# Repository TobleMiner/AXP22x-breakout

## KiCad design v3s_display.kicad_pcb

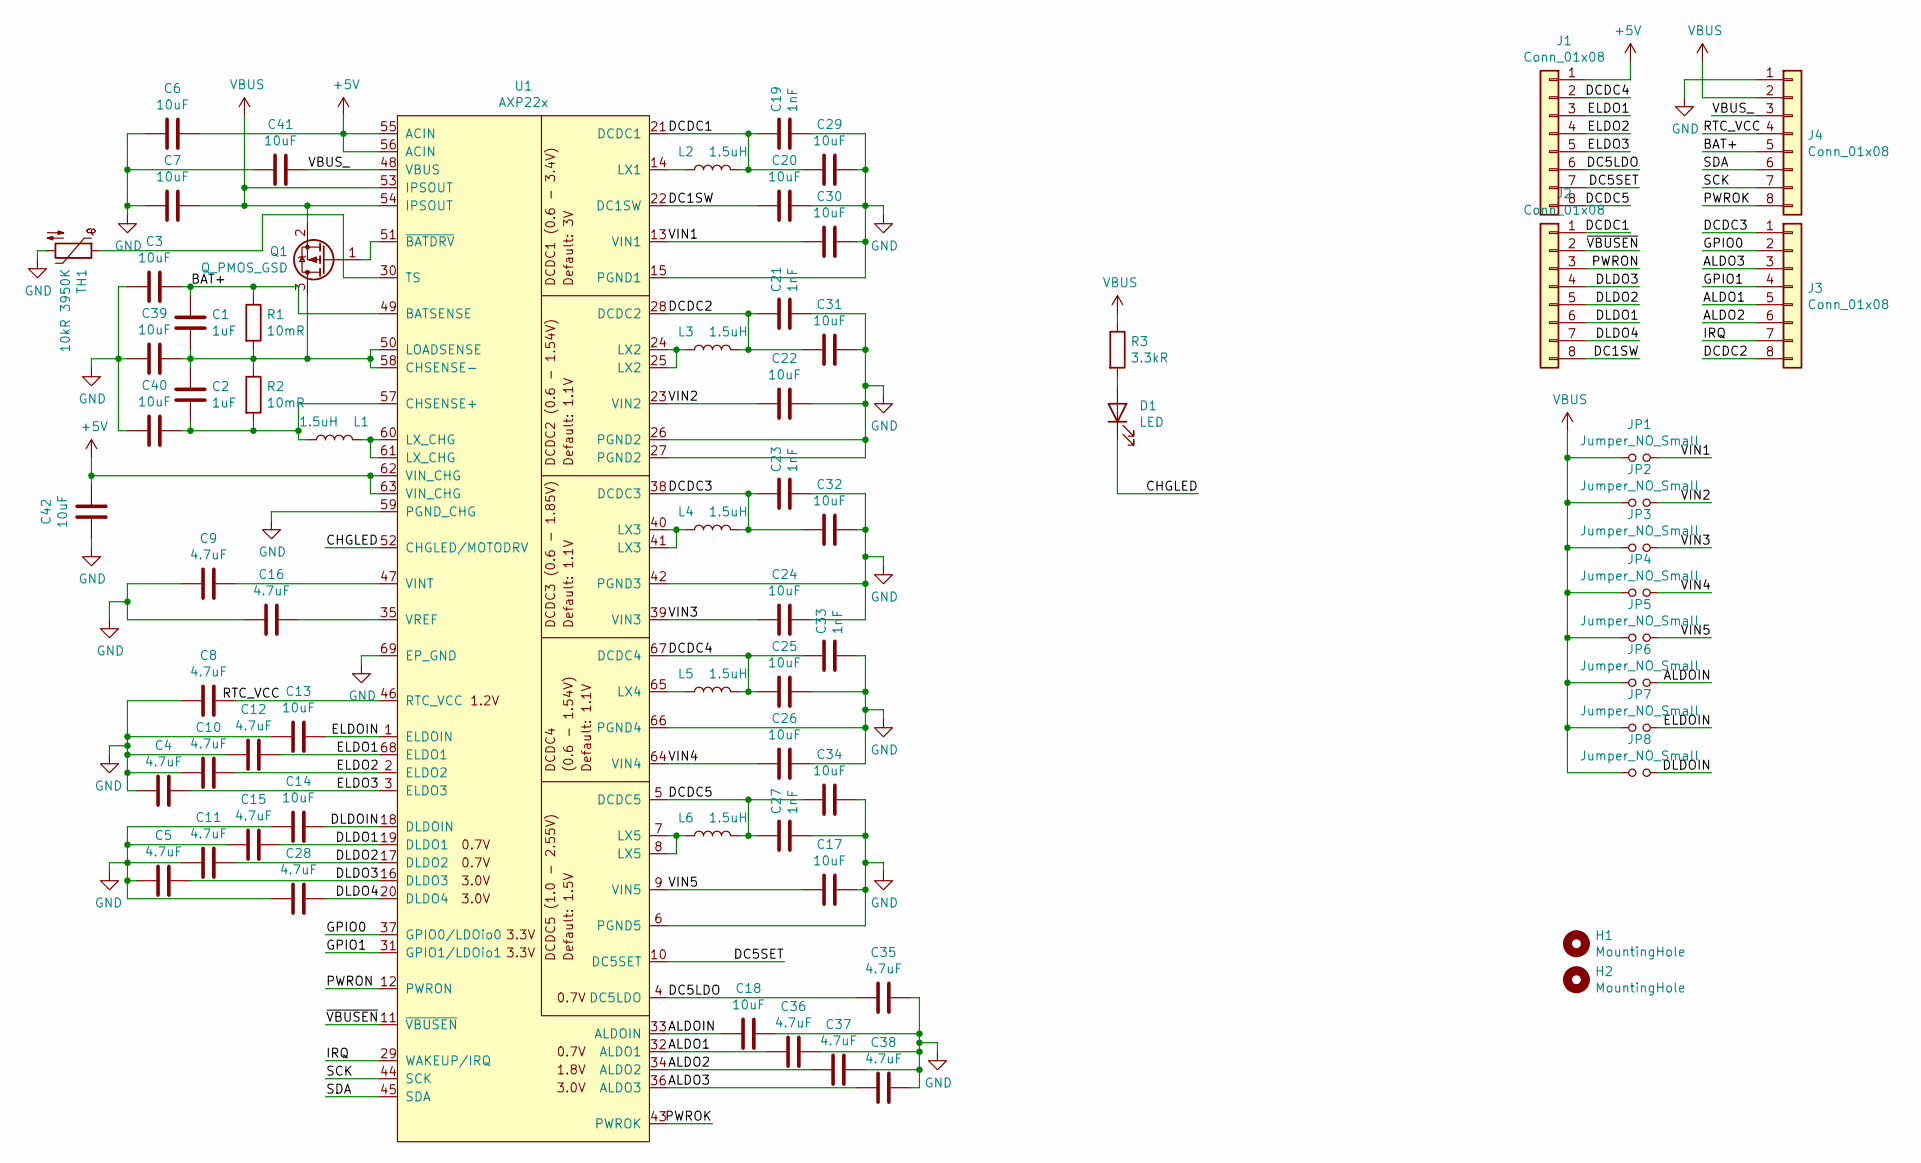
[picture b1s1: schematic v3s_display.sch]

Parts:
C1, C2: 1uF; C_0402_1005Metric; LCSC C52923
C3, C6, C7, C13, C14, C17, C18, C20, C22, C24, C25, C26, C29, C30, C31, C32, C34, C39, C40, C41, C42: 10uF; C_0603_1608Metric; LCSC C19702
C4, C5, C8, C9, C10, C11, C12, C15, C16, C28, C35, C36, C37, C38: 4.7uF; C_0402_1005Metric; LCSC C23733
C19, C21, C23, C27, C33: 1nF; C_0402_1005Metric; LCSC C1523
D1: LED; LED_0603_1608Metric; LCSC C2286
H1, H2: MountingHole; ToolingHole_JLCSMT
J1, J2, J3, J4: Conn_01x08; PinHeader_1x08_P2.54mm_Vertical
JP1, JP2, JP3, JP4, JP5, JP6, JP7, JP8: Jumper_NO_Small; PinHeader_1x02_P2.54mm_Vertical
L1, L2, L3, L4, L5, L6: 1.5uH; L_Taiyo-Yuden_MD-3030; LCSC C56594
Q1: Q_PMOS_GSD; SOT-23; LCSC C15127
R1, R2: 10mR; R_0805_2012Metric; LCSC C270927
R3: 3.3kR; R_0402_1005Metric; LCSC C25890
TH1: 10kR 3950K; R_0805_2012Metric; LCSC C51597
U1: AXP22x; QFN-68-1EP_8x8mm_P0.4mm_EP5.2x5.2mm_ThermalVias; LCSC C81850

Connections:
+5V: C6.1, C42.1, J1.1, U1.55 (ACIN), U1.56 (ACIN), U1.62 (VIN_CHG), U1.63 (VIN_CHG)
/ALDO1: C36.1, J3.5, U1.32 (ALDO1)
/ALDO2: C37.1, J3.6, U1.34 (ALDO2)
/ALDO3: C38.1, J3.3, U1.36 (ALDO3)
/ALDOIN: C18.2, JP6.2, U1.33 (ALDOIN)
/BAT+: C1.1, C3.1, J4.5, R1.1, U1.49 (BATSENSE)
/CHGLED: D1.1 (K), U1.52 (CHGLED/MOTODRV)
/DC1SW: C20.2, J2.8, U1.22 (DC1SW)
/DC5LDO: C35.1, J1.6, U1.4 (DC5LDO)
/DC5SET: J1.7, U1.10 (DC5SET)
/DCDC1: C19.1, C29.2, J2.1, L2.2, U1.21 (DCDC1)
/DCDC2: C21.1, C31.2, J3.8, L3.2, U1.28 (DCDC2)
/DCDC3: C23.1, C32.2, J3.1, L4.2, U1.38 (DCDC3)
/DCDC4: C25.2, C33.1, J1.2, L5.2, U1.67 (DCDC4)
/DCDC5: C27.1, C34.2, J1.8, L6.2, U1.5 (DCDC5)
/DLDO1: C15.2, J2.6, U1.19 (DLDO1)
/DLDO2: C11.2, J2.5, U1.17 (DLDO2)
/DLDO3: C5.2, J2.4, U1.16 (DLDO3)
/DLDO4: C28.2, J2.7, U1.20 (DLDO4)
/DLDOIN: C14.2, JP8.2, U1.18 (DLDOIN)
/ELDO1: C12.2, J1.3, U1.68 (ELDO1)
/ELDO2: C10.2, J1.4, U1.2 (ELDO2)
/ELDO3: C4.2, J1.5, U1.3 (ELDO3)
/ELDOIN: C13.2, JP7.2, U1.1 (ELDOIN)
/GPIO0: J3.2, U1.37 (GPIO0/LDOio0)
/GPIO1: J3.4, U1.31 (GPIO1/LDOio1)
/IRQ: J3.7, U1.29 (WAKEUP/IRQ)
/PWROK: J4.8, U1.43 (PWROK)
/PWRON: J2.3, U1.12 (PWRON)
/RTC_VCC: C8.2, J4.4, U1.46 (RTC_VCC)
/SCK: J4.7, U1.44 (SCK)
/SDA: J4.6, U1.45 (SDA)
/VBUS_: C41.1, J4.3, U1.48 (VBUS)
/VIN1: C30.2, JP1.2, U1.13 (VIN1)
/VIN2: C22.2, JP2.2, U1.23 (VIN2)
/VIN3: C24.2, JP3.2, U1.39 (VIN3)
/VIN4: C26.2, JP4.2, U1.64 (VIN4)
/VIN5: C17.2, JP5.2, U1.9 (VIN5)
/~VBUSEN: J2.2, U1.11 (~VBUSEN)
GND: C3.2, C4.1, C5.1, C6.2, C7.2, C8.1, C9.1, C10.1, C11.1, C12.1, C13.1, C14.1, C15.1, C16.1, C17.1, C18.1, C19.2, C20.1, C21.2, C22.1, C23.2, C24.1, C25.1, C26.1, C27.2, C28.1, C29.1, C30.1, C31.1, C32.1, C33.2, C34.1, C35.2, C36.2, C37.2, C38.2, C39.2, C40.2, C41.2, C42.2, J4.1, TH1.2, U1.6 (PGND5), U1.15 (PGND1), U1.26 (PGND2), U1.27 (PGND2), U1.42 (PGND3), U1.59 (PGND_CHG), U1.66 (PGND4), U1.69 (EP_GND)
unnamed: C1.2, C2.1, C39.1, Q1.3 (D), R1.2, R2.1, U1.50 (LOADSENSE), U1.58 (CHSENSE-)
unnamed: C2.2, C40.1, L1.2, R2.2, U1.57 (CHSENSE+)
unnamed: C9.2, U1.47 (VINT)
unnamed: C16.2, U1.35 (VREF)
unnamed: D1.2 (A), R3.2
unnamed: L1.1, U1.60 (LX_CHG), U1.61 (LX_CHG)
unnamed: L2.1, U1.14 (LX1)
unnamed: L3.1, U1.24 (LX2), U1.25 (LX2)
unnamed: L4.1, U1.40 (LX3), U1.41 (LX3)
unnamed: L5.1, U1.65 (LX4)
unnamed: L6.1, U1.7 (LX5), U1.8 (LX5)
unnamed: Q1.1 (G), U1.51 (~BATDRV)
unnamed: TH1.1, U1.30 (TS)
VBUS: C7.1, J4.2, JP1.1, JP2.1, JP3.1, JP4.1, JP5.1, JP6.1, JP7.1, JP8.1, Q1.2 (S), R3.1, U1.53 (IPSOUT), U1.54 (IPSOUT)

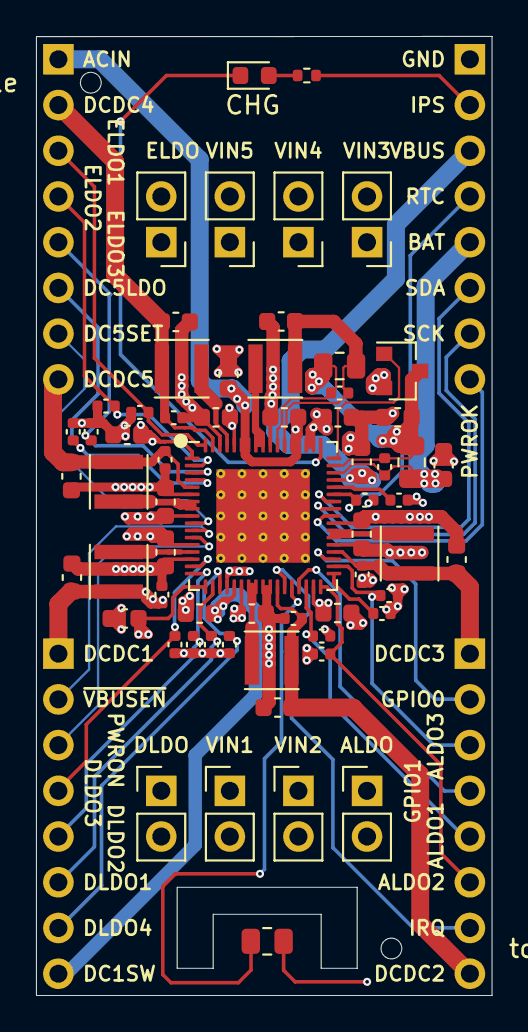
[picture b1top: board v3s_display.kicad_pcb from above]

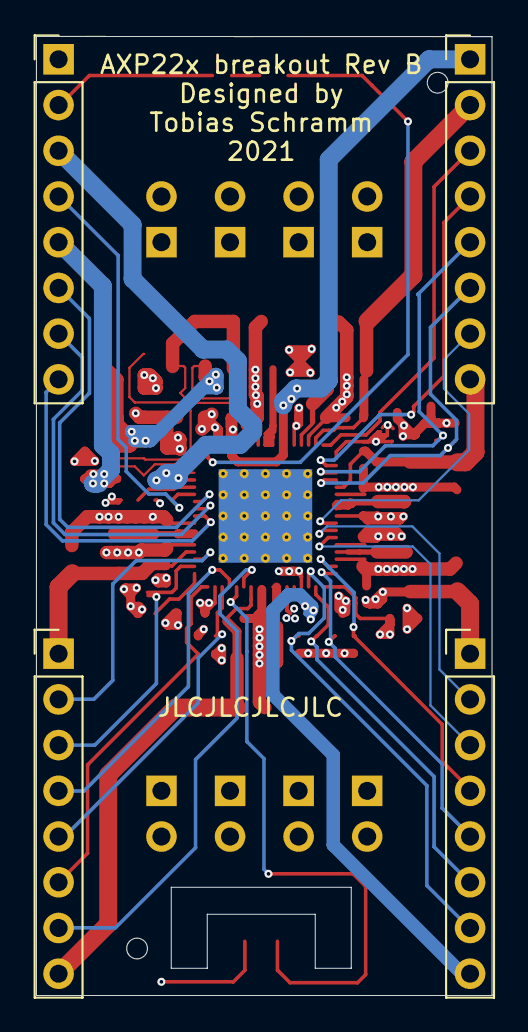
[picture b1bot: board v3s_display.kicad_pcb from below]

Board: 4 copper layers, 25.3 x 53.3 mm, 69 parts (4 on the bottom side), 54 nets.

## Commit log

2021-02-22 Add power jumper labels
2021-02-22 Fix silkscreen designators
2021-02-22 Add pin1 marker
2021-02-22 Add tooling holes
2021-02-22 Add footprint library table
2021-03-02 Annotate mounting holes
2021-03-02 Improve power routing a little
2021-03-02 Increase trace width on LDOs
